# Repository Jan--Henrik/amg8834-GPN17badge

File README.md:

# amg8834-GPN17badge

amg8834 addon for GPN17 badge

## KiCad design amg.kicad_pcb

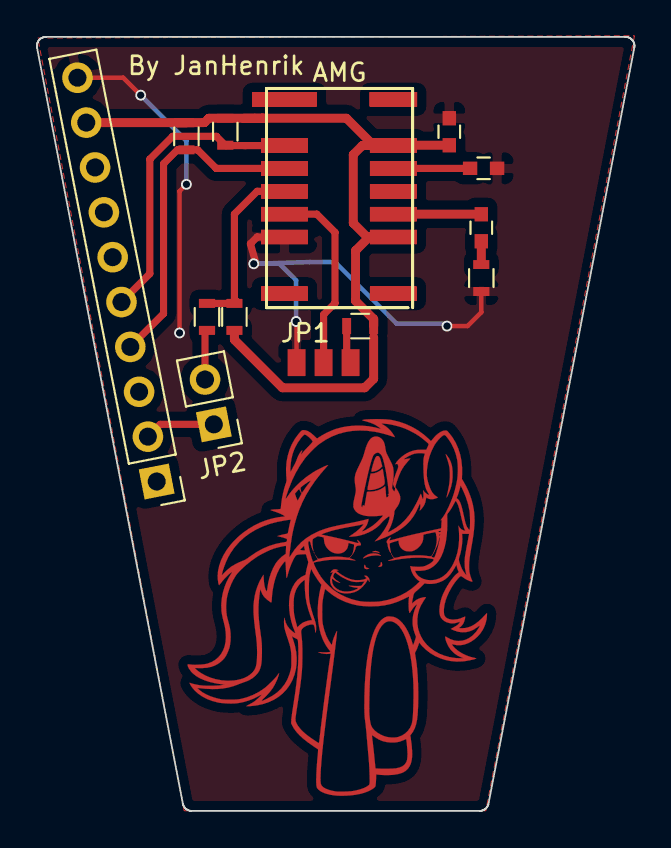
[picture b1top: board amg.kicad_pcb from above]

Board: 2 copper layers, 33.2 x 43.0 mm, 13 parts (1 on the bottom side), 12 nets.

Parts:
1.5µF1, 1µF1, 10µ11: C_Small; C_0603
10KOhm1, 10KOhm2, 10KOhm3, 10KOhm4: R; R_0603
20Ohm1: R_Small; R_0603
>470OHM1: R_Small; R_0603
AMG: AMG8834; GridEyeSensor
J1: CONN_01X10; Pin_Header_Straight_1x10_Pitch2.54mm
JP1: Adress select; SOLDER_JUMPER_3
JP2: Jumper; Pin_Header_Straight_1x02_Pitch2.54mm

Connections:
AD_SELECT: AMG.5, JP1.2
GND: 1.5µF1.2, 10µ11.2, 20Ohm1.2, AMG.6, J1.10, JP1.3
INT: 10KOhm2.2, >470OHM1.1, AMG.4
INT_B: J1.2, JP2.1
unnamed: 1.5µF1.1, AMG.12
unnamed: 1µF1.1, 20Ohm1.1
unnamed: 1µF1.2, AMG.10
unnamed: 10KOhm1.2, JP1.1
unnamed: >470OHM1.2, JP2.2
SCL: 10KOhm3.2, AMG.3, J1.4
SDA: 10KOhm4.2, AMG.2, J1.5
VDD: 10KOhm1.1, 10KOhm2.1, 10KOhm3.1, 10KOhm4.1, 10µ11.1, AMG.9, AMG.13, J1.9

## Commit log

2019-02-26 added kicad files
2019-02-26 added image
